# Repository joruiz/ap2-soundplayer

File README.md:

ap2-soundplayer
===============

Sound player module for the Agile Prototyping Plaltform

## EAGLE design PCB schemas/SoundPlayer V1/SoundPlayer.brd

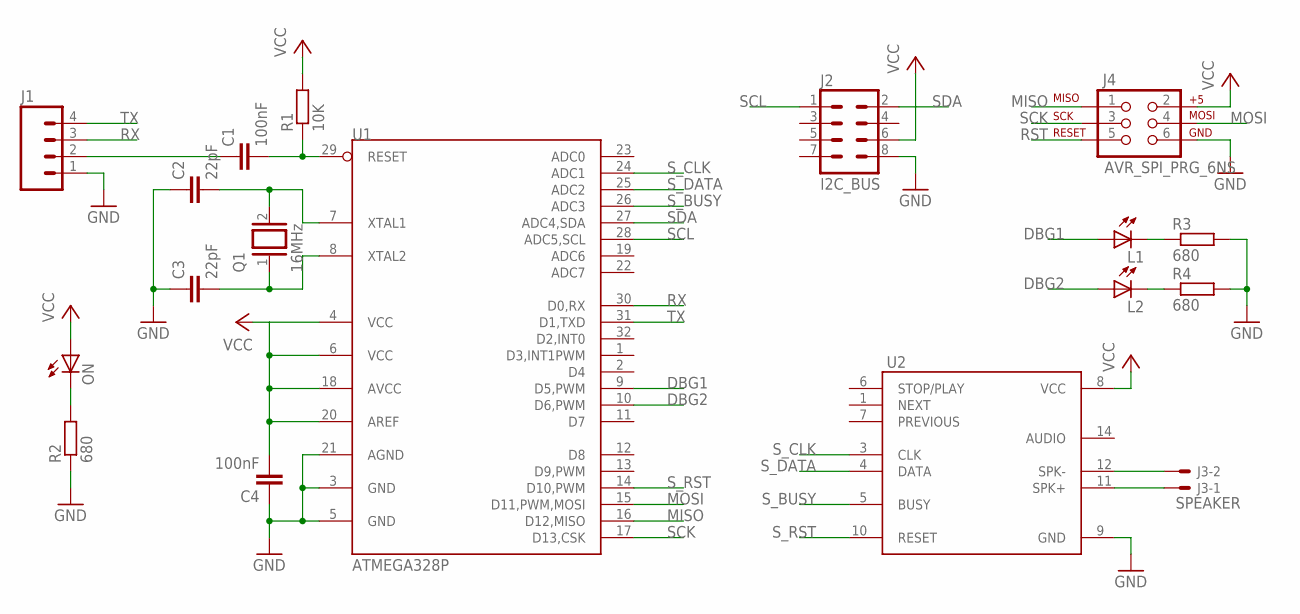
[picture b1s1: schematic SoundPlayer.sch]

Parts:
C1, C4: 100nF; C0805
C2, C3: 22pF; C0805
J1: M04PTH; 1X04
J2: I2C_BUS; SOCKET04X2_ANGLE
J3: SPEAKER; 7395-02
J4: AVR_SPI_PRG_6NS; 2X3-NS
L1, L2: LEDCHIPLED_0805; CHIPLED_0805
ON: LEDCHIPLED_0805; CHIPLED_0805
Q1: 16MHz; QS
R1: 10K; R0805
R2, R3, R4: 680; R0805
U1: ATMEGA328P; TQFP32-08
U2: SOMO-14D

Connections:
DBG1: L1.A, U1.9 (D5,PWM)
DBG2: L2.A, U1.10 (D6,PWM)
GND: C2.1, C3.1, C4.1, J1.1, J2.8, J4.6, R2.1, R3.2, R4.2, U1.3 (GND), U1.5 (GND), U1.21 (AGND), U2.9 (GND)
L2: L2.C, R4.1
MISO: J4.1, U1.16 (D12,MISO)
MOSI: J4.4, U1.15 (D11,PWM,MOSI)
unnamed: C1.1, J1.2
unnamed: J3.2, U2.12 (SPK-)
unnamed: J3.1, U2.11 (SPK+)
unnamed: C2.2, Q1.2, U1.7 (XTAL1)
unnamed: C3.2, Q1.1, U1.8 (XTAL2)
unnamed: ON.C, R2.2
unnamed: L1.C, R3.1
RST: C1.2, J4.5, R1.1, U1.29 (RESET)
RX: J1.3, U1.30 (D0,RX)
SCK: J4.3, U1.17 (D13,CSK)
SCL: J2.1, U1.28 (ADC5,SCL)
SDA: J2.2, U1.27 (ADC4,SDA)
S_BUSY: U1.26 (ADC3), U2.5 (BUSY)
S_CLK: U1.24 (ADC1), U2.3 (CLK)
S_DATA: U1.25 (ADC2), U2.4 (DATA)
S_RST: U1.14 (D10,PWM), U2.10 (RESET)
TX: J1.4, U1.31 (D1,TXD)
VCC: C4.2, J2.6, J4.2, ON.A, R1.2, U1.4 (VCC), U1.6 (VCC), U1.18 (AVCC), U1.20 (AREF), U2.8 (VCC)

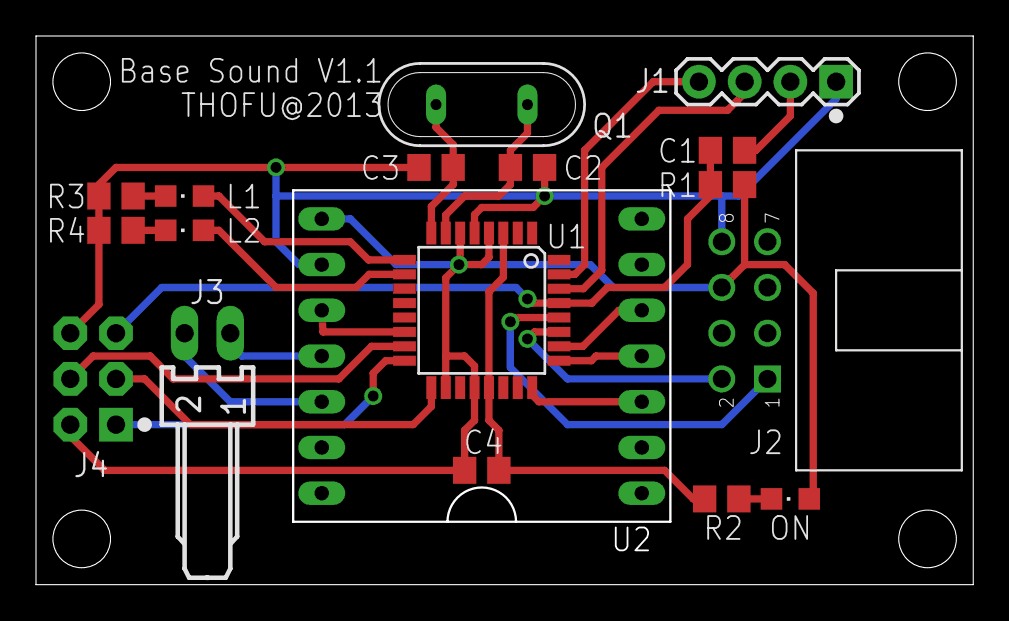
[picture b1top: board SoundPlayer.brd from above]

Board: 2 copper layers, 51.9 x 30.4 mm, 18 parts (0 on the bottom side), 24 nets.

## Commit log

2014-06-05 Added Version 1 of the sound player peripheral

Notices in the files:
parts and their libraries:
SparkFun-Connectors: Licensing: CC v3.0 Share-Alike You are welcome to use this library for commercial purposes.
